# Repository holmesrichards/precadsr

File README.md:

# Kassutronics Precision ADSR with retriggering and looping modifications

This is an ADSR envelope generator synth module. Layout and panel are Kosmo format. 

The main part of the design is from [Kassutronics](https://kassu2000.blogspot.com/2015/05/precision-adsr.html), who in turn based it on the YuSynth [ADSR (version 2)](http://yusynth.net/Modular/EN/ADSR/index_new.html), which is similar to René Schmitz's [Fastest Envelope In the West](https://www.schmitzbits.de/adsr.html). The latter two, like some other envelope generators, have the problem that the voltage releases very slowly after reaching about 700 mV, taking several seconds or longer to drop below 100 mV. Kassutronics fixed this by replacing the decay and release diodes with precision rectifiers (op amp with diode in the feedback loop). Another modification was a clever way of combining the LED indicator with the inverted envelope output using a single op amp.

The present design adds the following features:

* Two switch selectable capacitors for slower and faster time scales (restoring a feature of the YuSynth ADSR, though without the two resistors in the attack path).
* Capacitors can be socketed for experimentation, soldered, or socketed at first and soldered later.
* Retriggering input, allowing additional attack/decay peaks on top of the sustain (inspired by but simplified from Benjamin AM's [design](https://electro-music.com/forum/post-372492.html#372492)).
* Looping mode, allowing attack-decay envelopes to repeat as long as a gate is present, or, if nothing is plugged into the gate input, indefinitely. This can be used as a sequence of envelopes or as a kind of odd LFO.

## Current draw
12 mA +12 V, 10 mA -12 V

## Photos

## Documentation:

* [Schematic](Docs/precadsr.pdf)
* PCB layout: [front](Docs/precadsr_layout_front.pdf), [back](Docs/precadsr_layout_back.pdf)
* [BOM](Docs/precadsr_bom.md)
* [Build notes](Docs/build.md)
* [How to use](Docs/use.md)

## GitHub repository

* [https://github.com/holmesrichards/precadsr](https://github.com/holmesrichards/precadsr)

## Submodules

This repo uses submodules aoKicad and Kosmo_panel, which provide needed libaries for KiCad. To clone:

```
git clone git@github.com:holmesrichards/precadsr.git
git submodule init
git submodule update
```

Alternatively do

```
git clone --recurse-submodules git@github.com:holmesrichards/precadsr.git
```

Or if you download the repository as a zip file, you must also click on the "aoKicad" and "Kosmo\_panel" links on the GitHub page (they'll have "@ something" after them) and download them as separate zip files which you can unzip into the aoKicad and Kosmo\_panel directories.

If desired, copy the files from aoKicad and Kosmo\_panel to wherever you prefer (your KiCad user library directory, for instance, if you have one). Then in KiCad, add symbol libraries 

```
aoKicad/ao_symbols
Kosmo_panel/Kosmo
```
and footprint libraries 
```
aoKicad/ao_tht
Kosmo_panel/Kosmo_panel.
```

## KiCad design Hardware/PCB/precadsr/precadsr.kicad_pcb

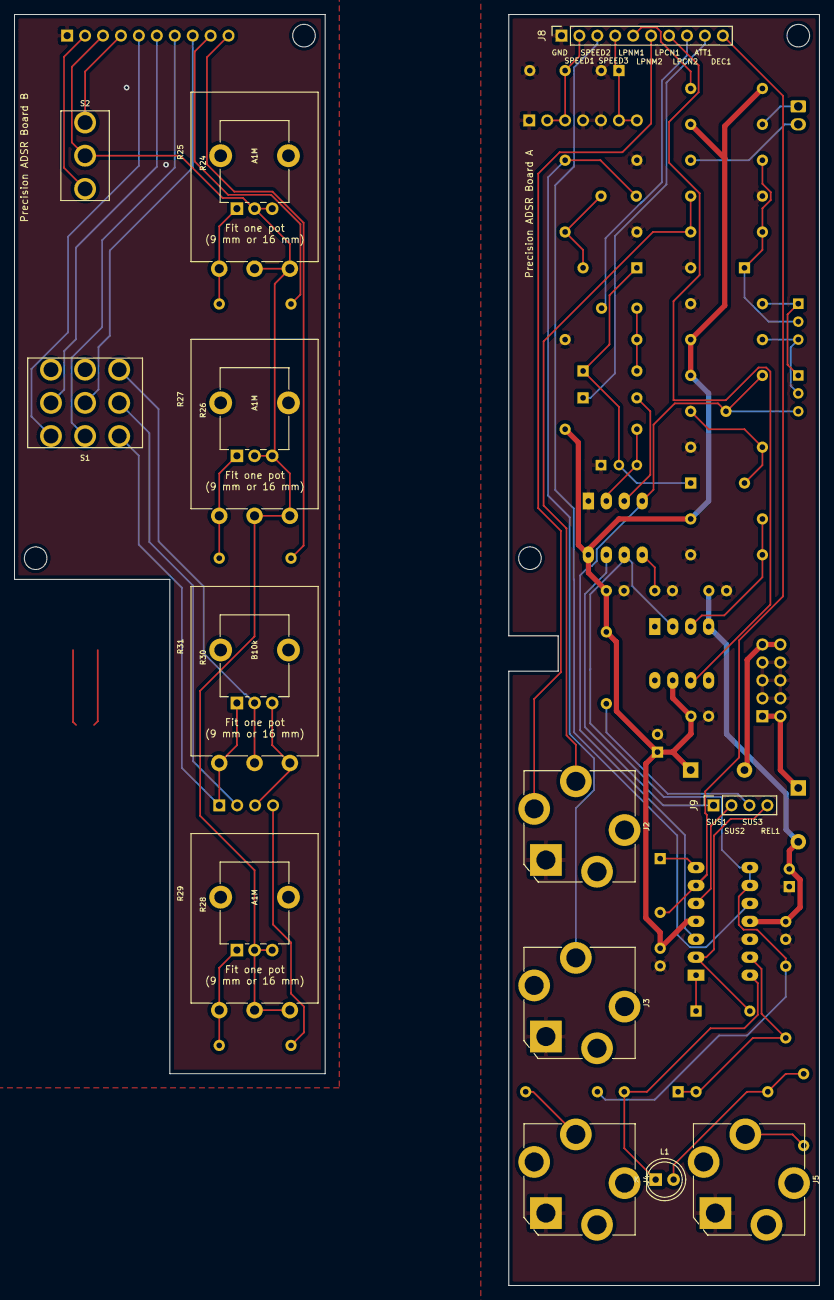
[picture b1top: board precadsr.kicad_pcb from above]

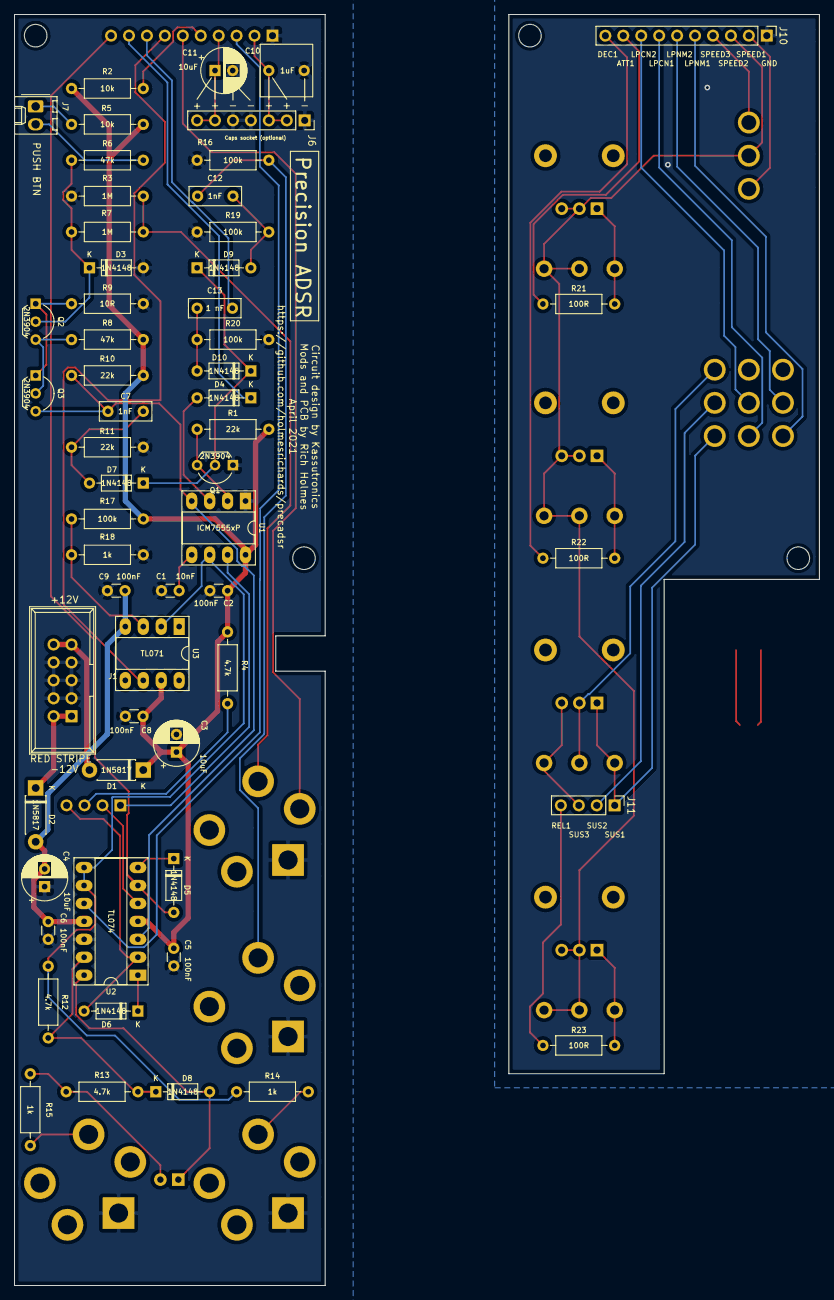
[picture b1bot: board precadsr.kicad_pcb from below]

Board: 2 copper layers, 114.0 x 180.0 mm, 80 parts (57 on the bottom side), 59 nets.

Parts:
C1: 10nF; C_Disc_D3.0mm_W1.6mm_P2.50mm
C2, C5, C6, C8, C9: 100nF; C_Disc_D3.0mm_W1.6mm_P2.50mm
C3, C4, C11: 10uF; CP_Radial_D6.3mm_P2.50mm
C7, C12: 1nF; C_Rect_L7.2mm_W2.5mm_P5.00mm_FKS2_FKP2_MKS2_MKP2
C10: 1uF; C_Rect_L7.2mm_W7.2mm_P5.00mm_FKS2_FKP2_MKS2_MKP2
C13: 1 nF; C_Rect_L7.2mm_W2.5mm_P5.00mm_FKS2_FKP2_MKS2_MKP2
D1, D2: 1N5817; D_DO-41_SOD81_P7.62mm_Horizontal
D3, D4, D5, D6, D7, D8, D9, D10: 1N4148; D_DO-35_SOD27_P7.62mm_Horizontal
GRAF1, GRAF2: Panel holes; precadsr-panel-holes
H1, H2, H3, H4: MountingHole; MountingHole_3.2mm_M3
J1: Synth_power_2x5; Power_Header
J2: AudioJack2_SwitchT; Jack_6.35mm_PJ_629HAN
J3, J4, J5: AudioJack2; Jack_6.35mm_PJ_629HAN
J6: Conn_01x07; PinSocket_1x07_P2.54mm_Vertical
J7: 2_pin_Molex_header; Molex_KK-254_AE-6410-02A_1x02_P2.54mm_Vertical
J8: Conn_01x10; PinSocket_1x10_P2.54mm_Vertical
J9: Conn_01x04; PinSocket_1x04_P2.54mm_Vertical
J10: Conn_01x10; PinHeader_1x10_P2.54mm_Vertical
J11: Conn_01x04; PinHeader_1x04_P2.54mm_Vertical
L1: LED; LED_D5.0mm
Q1, Q2, Q3: 2N3904; TO-92_Inline_Wide
R1, R10, R11: 22k; R_Axial_DIN0207_L6.3mm_D2.5mm_P10.16mm_Horizontal
R2, R5: 10k; R_Axial_DIN0207_L6.3mm_D2.5mm_P10.16mm_Horizontal
R3, R7: 1M; R_Axial_DIN0207_L6.3mm_D2.5mm_P10.16mm_Horizontal
R4, R12, R13: 4.7k; R_Axial_DIN0207_L6.3mm_D2.5mm_P10.16mm_Horizontal
R6, R8: 47k; R_Axial_DIN0207_L6.3mm_D2.5mm_P10.16mm_Horizontal
R9: 10R; R_Axial_DIN0207_L6.3mm_D2.5mm_P10.16mm_Horizontal
R14, R15, R18: 1k; R_Axial_DIN0207_L6.3mm_D2.5mm_P10.16mm_Horizontal
R16, R17, R19, R20: 100k; R_Axial_DIN0207_L6.3mm_D2.5mm_P10.16mm_Horizontal
R21, R22, R23: 100R; R_Axial_DIN0207_L6.3mm_D2.5mm_P10.16mm_Horizontal
R24, R26, R28: A1M; Potentiometer_Alpha_RD901F-40-00D_Single_Vertical_CircularH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
R25, R27, R29: A1M; Potentiometer_Alpha_16mm_Single_Vertical
R30: B10k; Potentiometer_Alpha_RD901F-40-00D_Single_Vertical_CircularH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
R31: B10k; Potentiometer_Alpha_16mm_Single_Vertical
S1: SW_3PDT_x3; 3PDT-toggle-switch-1M-seriesx
S2: SW_SPDT; SPDT-toggle-switch-1M-series
U1: ICM7555xP; DIP-8_W7.62mm_Socket_LongPads
U2: TL074; DIP-14_W7.62mm_Socket_LongPads
U3: TL071; DIP-8_W7.62mm_Socket_LongPads

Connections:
+12V: C2.1, C3.1, C5.1, C8.1, D1.1, R1.1, R2.2, R4.2, R5.1, R8.2, R10.2, R17.2, U1.8, U2.4, U3.7
-12V: C4.2, C6.2, C9.2, D2.2, U2.11, U3.4
/+12_IN: D1.2, J1.9, J1.10
/-12_IN: D2.1, J1.1, J1.2
/GIN: J2.T, R3.2, R7.2
/TIN: C12.2, J3.T, R16.2
ATT1: D4.1, J8.9
ATT1_P: J10.9, R21.2
DEC1: D5.2, J8.10, U2.6
DEC1_P: J10.10, R22.2
GATE: C7.2, Q3.3, R10.1, U1.4, U2.3
GND: C1.2, C2.2, C3.2, C4.1, C5.2, C6.1, C8.2, C9.1, C10.1, C11.2, D3.2, J1.3, J1.4, J1.5, J1.6, J1.7, J1.8, J2.S, J3.S, J4.S, J5.S, J6.1, J6.4, J6.5, J8.1, Q1.1, R3.1, R9.1, R11.1, R16.1, R18.1, R19.1, R20.1, U1.1, U2.12
LOOP_CONN_1: J8.7, U3.6
LOOP_CONN_1_P: J10.7, S1.6
LOOP_CONN_2: C13.2, J8.8
LOOP_CONN_2_P: J10.8, S1.5
LOOP_NORM_1: J8.5, R2.1
LOOP_NORM_1_P: J10.5, S1.3
LOOP_NORM_2: J2.TN, J8.6
LOOP_NORM_2_P: J10.6, S1.2
unnamed: C1.1, U1.5
unnamed: C7.1, D7.2, R11.2
unnamed: C12.1, D9.2, R19.2
unnamed: C13.1, D10.2, R20.2
unnamed: D3.1, Q2.2, R6.1, R7.1
unnamed: D4.2, U1.3
unnamed: D5.1, U2.7
unnamed: D6.1, U2.1
unnamed: D8.1, R12.2, R13.2, U2.13
unnamed: D8.2, L1.1, U2.14
unnamed: J4.T, R14.1
unnamed: J5.T, R15.1
unnamed: L1.2, R13.1, R15.2
unnamed: Q1.3, R1.2, U1.2
unnamed: Q2.1, Q3.1, R9.2
unnamed: Q2.3, Q3.2, R8.1
unnamed: R17.1, R18.2, U3.3
unnamed: R21.1, R24.1, R25.1
unnamed: R22.1, R26.1, R27.1
unnamed: R23.1, R28.1, R29.1
POTS: J8.3, U2.10
POTS_P: J10.3, R24.2, R24.3, R25.2, R25.3, R26.2, R26.3, R27.2, R27.3, R28.2, R28.3, R29.2, R29.3, S2.2
PUSH_1: J7.1, R5.2
PUSH_2: J7.2, R6.2
REL1: D6.2, J9.4, U2.2
REL1_P: J11.4, R23.2
SPEED_1: C10.2, J6.2, J6.3, J8.2
SPEED_1_P: J10.2, S2.1
SPEED_3: C11.1, J6.6, J6.7, J8.4
SPEED_3_P: J10.4, S2.3
SUS1: J9.1, U1.7
SUS1_P: J11.1, R30.1, R31.1, S1.9
SUS2: J9.2, U2.5
SUS2_P: J11.2, S1.8
SUS2_S: R30.2, R31.2, S1.7
SUS3: J9.3, R4.1
SUS3_P: J11.3, R30.3, R31.3
THR: R12.1, R14.2, U1.6, U2.8, U2.9, U3.2
TRIG: D7.1, D9.1, D10.1, Q1.2

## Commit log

2021-04-21 Initial version
2021-04-28 Various tweaks
2021-04-30 Add comments and graphics symbols to schematics
2021-05-10 Optional capacitor socket
2021-05-21 Change op amp, dims to user drawings
2021-07-29 Footprints, PCB update
2021-08-07 Final tweaks before fabbing; Kosmo_panel lib update
2021-08-12 submodules
2021-08-12 Create LICENSE
2021-08-12 github url
2021-08-12 KiCad lib tables
2021-08-12 submodule update
2021-08-12 schematics tweaks
2021-08-16 Gerbers
2021-08-19 Submodules, improved NPTH
2021-08-19 NPTH new version
2021-08-20 Kosmo_panel
2021-08-21 relocate libraries
2021-08-21 rm al panel
2021-08-21 rm project libraries
2021-08-27 submodule doc
2021-08-29 Documentation, some cosmetic sh/PCB updates
2021-08-31 Build images
2021-09-01 Documentation
2021-09-01 README
2021-09-02 Images, docs updates
2021-09-03 Change C13 to 10 nF
2021-09-03 README correction and edits
2021-09-03 Update libraries
2021-09-06 How to use
2021-09-15 SVG decontamination
2021-09-18 Button color, image location
2021-12-11 Extend trigger mod block to include diode
2021-12-24 Current draw
